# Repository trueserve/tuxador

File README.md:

# Tuxador

A simple, secure door entry/open counter.

Still in the planning phase.

## Goals

- Make a basic, cost-effective counter
- Use an easy platform (this project will be used to teach)
- Support one doorway and a tamper switch, or two doorways
- Support proper security open/close/tamper/short loop
- Configurable ability to modify or reset the counter
- Indicate power on time, last tamper/short, last open
- All indications on inexpensive LCD display
- Directly mounts to common 16x2 character display or 1.8" Color LCD
- PCB design allows for destroying debugging interfaces
- 4-layer PCB, in cheap fab size, to bury any programming / debugging traces

## What is this useful for?

Some potential uses of this project include:

- Secure doors or closets with internal access logs
- Door entry audible alarm
- Generic upcounter for anything one might use one for

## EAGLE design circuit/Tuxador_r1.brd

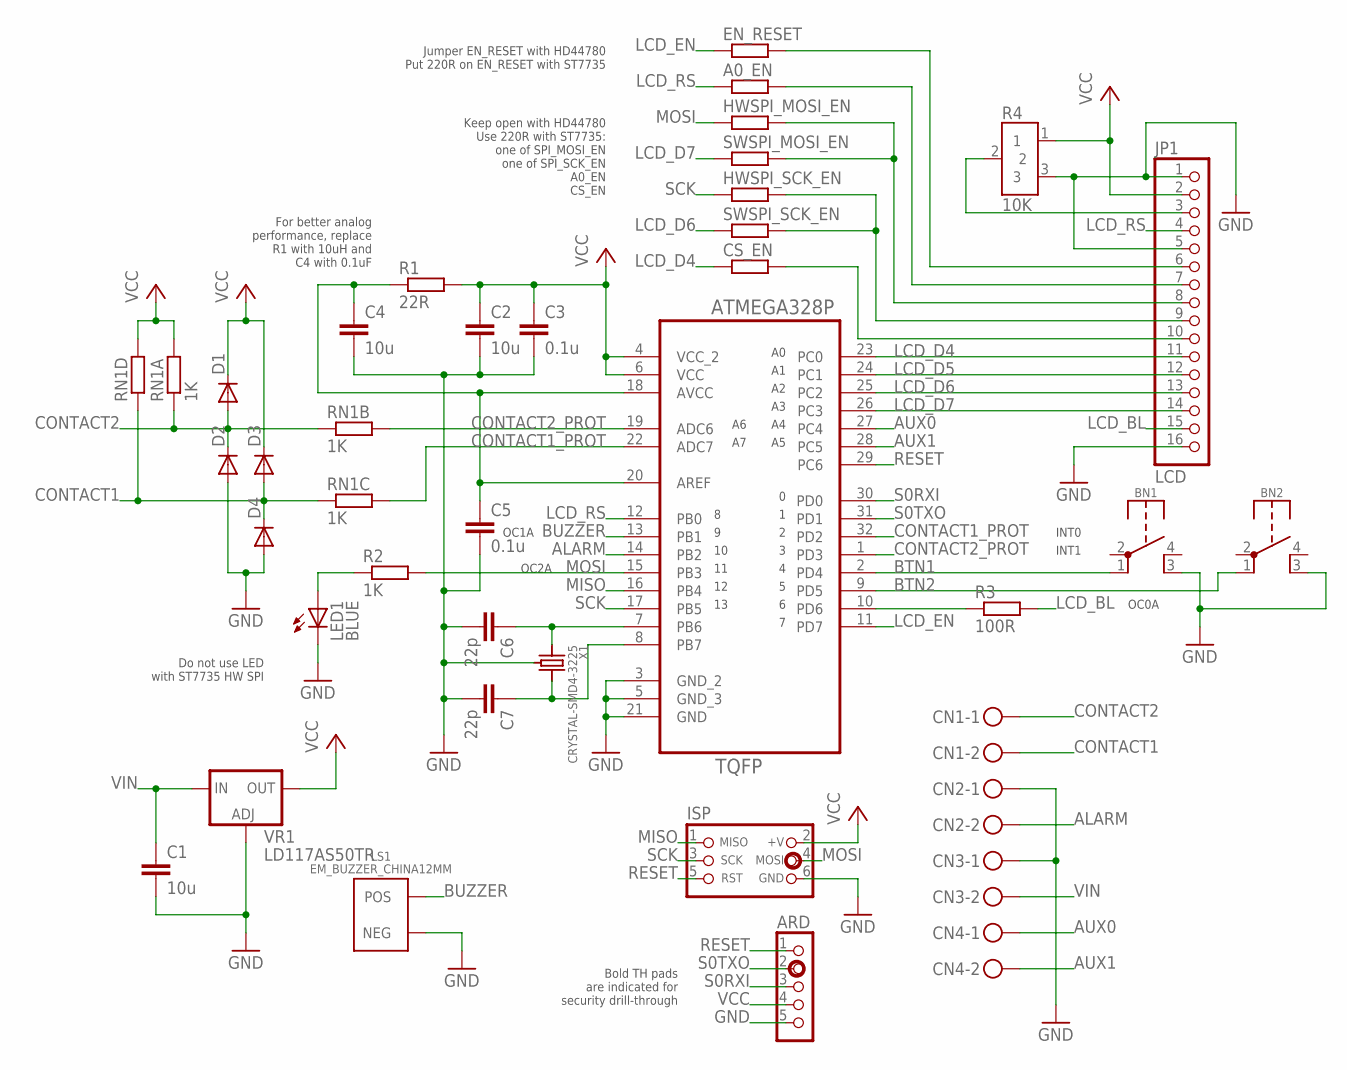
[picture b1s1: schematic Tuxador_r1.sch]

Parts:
A0_EN: -0-; R1206
ARD: CON_HEADER_1X05-PTH; M1X5
BN1, BN2: SCHURTER_PUSHBTN_LPH; SCHURTER_LPH
C1, C2, C4: 10u; C0805
C3, C5: 0.1u; C0805
C6, C7: 22p; C0603
CN1, CN2, CN3, CN4: MKDSN1,5/2-5,08
CS_EN: -0-; R1206
D1, D2, D3, D4: DIODE-SOT23; SOT-23
EN_RESET: -0-; R1206
HWSPI_MOSI_EN: -0-; R1206
HWSPI_SCK_EN: -0-; R1206
ISP: CON_HEADER_PRG_AVR_ICSP_NOLBL; HEADER_PRG_2X03_NOLBL
JP1: LCD; 1X16
LED1: BLUE; LED-3MM
LS1: EM_BUZZER_CHINA12MM; CHINA_ELECTRO_SOUNDER_12MM
R1: 22R; R1206
R2: 1K; R1206
R3: 100R; R1206
R4: 10K; BI-TECH_36P-POT
RN1: 1K; RN8P-4R-CRA06S
SWSPI_MOSI_EN: -0-; R1206
SWSPI_SCK_EN: -0-; R1206
U1: ATMEGA328P-AU; QFP80P900X900X120-32N
VR1: LD117AS50TR; SOT223
X1: CRYSTAL-SMD4-3225; 3.2X2.5MM

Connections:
ALARM: CN2.2, U1.14 (PB2)
AUX0: CN4.1, U1.27 (PC4)
AUX1: CN4.2, U1.28 (PC5)
AVCC: C4.1, C5.1, R1.1, U1.18 (AVCC), U1.20 (AREF)
BTN1: BN1.1, U1.2 (PD4)
BTN2: BN2.1, U1.9 (PD5)
BUZZER: LS1.POS, U1.13 (PB1)
CONTACT1: CN1.2, D3.1 (A), D4.3 (C), RN1.3 (1), RN1.4 (1)
CONTACT1_PROT: RN1.6 (2), U1.22 (ADC7), U1.32 (PD2)
CONTACT2: CN1.1, D1.1 (A), D2.3 (C), RN1.1, RN1.2 (1)
CONTACT2_PROT: RN1.7 (2), U1.1 (PD3), U1.19 (ADC6)
GND: ARD.5, BN1.3, BN2.3, C1.2, C2.2, C3.2, C4.2, C5.2, C6.2, C7.2, CN2.1, CN3.1, D2.1 (A), D4.1 (A), ISP.6 (GND), JP1.1, JP1.5, JP1.16, LED1.K (C), LS1.NEG, R4.3, U1.3 (GND_2), U1.5 (GND_3), U1.21 (GND), VR1.1 (ADJ), X1.2 (GND), X1.4 (GND)
LCD_BL: JP1.15, R3.2
LCD_BL_MCU: R3.1, U1.10 (PD6)
LCD_D4: CS_EN.1, JP1.11, U1.23 (PC0)
LCD_D5: JP1.12, U1.24 (PC1)
LCD_D6: JP1.13, SWSPI_SCK_EN.1, U1.25 (PC2)
LCD_D7: JP1.14, SWSPI_MOSI_EN.1, U1.26 (PC3)
LCD_EN: EN_RESET.1, U1.11 (PD7)
LCD_EN_RESET: EN_RESET.2, JP1.6
LCD_RS: A0_EN.1, JP1.4, U1.12 (PB0)
MISO: ISP.1 (MISO), U1.16 (PB4)
MOSI: HWSPI_MOSI_EN.1, ISP.4 (MOSI), R2.2, U1.15 (PB3)
unnamed: LED1.A, R2.1
unnamed: JP1.3, R4.2
unnamed: A0_EN.2, JP1.7
unnamed: HWSPI_MOSI_EN.2, JP1.8, SWSPI_MOSI_EN.2
unnamed: HWSPI_SCK_EN.2, JP1.9, SWSPI_SCK_EN.2
unnamed: CS_EN.2, JP1.10
OSC1: C6.1, U1.7 (PB6), X1.1
OSC2: C7.1, U1.8 (PB7), X1.3 (2)
RESET: ARD.1, ISP.5 (RST), U1.29 (PC6)
S0RXI: ARD.3, U1.30 (PD0)
S0TXO: ARD.2, U1.31 (PD1)
SCK: HWSPI_SCK_EN.1, ISP.3 (SCK), U1.17 (PB5)
VCC: ARD.4, C2.1, C3.1, D1.3 (C), D3.3 (C), ISP.2 (+V), JP1.2, R1.2, R4.1, RN1.5 (2), RN1.8 (2), U1.4 (VCC_2), U1.6 (VCC), VR1.4 (OUT)
VIN: C1.1, CN3.2, VR1.3 (IN)

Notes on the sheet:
For better analog performance, replace R1 with 10uH and C4 with 0.1uF
OC0A
OC1A
INT0
INT1
OC2A
Jumper EN_RESET with HD44780 Put 220R on EN_RESET with ST7735
Keep open with HD44780 Use 220R with ST7735: one of SPI_MOSI_EN one of SPI_SCK_EN A0_EN CS_EN
Do not use LED with ST7735 HW SPI
Bold TH pads are indicated for security drill-through

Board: 2 copper layers, 37 parts (15 on the bottom side), 37 nets, no tracks yet.

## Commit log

2014-10-25 :neckbeard: Added .gitattributes
2014-10-25 Initial schematic
    This is the initial schematic for the door counter project.
    Also have an incomplete BOM and some implementation ideas.
    Decided on possible Arduino compatibility not because it is best for the
    job, but because it is barely capable and others know how to work on it.
    BOM is probably $2 higher and programming will probably be buggier an
    take longer because of this. Still have time to determine if this should
2014-10-25 Update README.md
    Minor formatting changes
2014-10-25 Remove redundant pull-up resistors
    Removed redundant R6 and R7 contact pull-up resistors
2014-10-26 Reorganized files
    - Renamed pcb/ to circuit/
    - Moved ideas.txt to root
2014-10-26 Added .gitignore
    Ignoring Eagle automatic backups of schematics, boards and libraries
2014-10-27 Updated ideas.txt
    Idea for testing to make sure the analog pins have not been damaged, as
    there is minimal protection
2014-10-27 Add clamping diodes
    Clamping diodes have been added to the contact inputs.
    Support for ST7735-compatible LCDs has been added to the main LCD
    header.
2014-10-27 Initial code added
    Absolutely nothing here yet, but setting up the layout / formatting and
    some pin defines for the LCD interface.
2014-10-27 Minor schematic updates
    - Cleaned up some sections
    - Added more descriptive text
    - Indicated drill-through holes for security on programming headers.
    These will be located on their own section on the board but depending on
    board costs to mill these sections I want to indicate where a drill can
    be used.
2014-10-28 Added tuxavant copyright info
    It's what was given
2014-10-29 Added resistors for clamping diode protection
    Oops
2014-10-31 Component update; initial board layout
    Components have been updated as necessary for the design. Examples are
    changing the voltage regulator and the crystal.
    Initial board component placement. Still a lot of work to do here before
    running traces.
